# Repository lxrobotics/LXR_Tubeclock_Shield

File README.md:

LXRobotics P4 TubeClockShield
==============

# Image

# Description

A Tube Clock is defined as a clock showing the time on a so-called Vacuum Fluorescent Display (VFD). The exact operation of VFDs is described on Wikipedia vividly. The VFDs were developed in the 1960s in Japan and replaced the Nixie tubes which were functioning based on glow lamps principle. Today VFDs, because of their retro looks, are primarily used by hobbyists for clocks construction and other electronic projects. The LXRobotics Tubeclock Shield allows, in combination with an Arduino Uno Board, the construction of such tube clock. For the quick start, Arduino libraries are available with sample programs.

**Features**

* Tube voltage adjustable from 30 to 70 V
* I2C-Real Time Clock  (RTC) for clock functionality
* Brightness sensor (LDR =Light Dependent Resistor)
* Temperature sensor (NTC-Thermistor)
* Connections for 2 button/switch
* Connection for external backup baterry for keeping the current time also at power failure (external backup battery is not included in the delivery)
* Exclusively screw terminals for simple yet stable connection of cables to the board available
* Arduino Library available for control of Tubeclock Shield with example programms
* Arduino Library available for the usage of Tubeclock Shield with a IV-18 Tube
* Arduino Library for conversion of the temperature sensor - tube data in °C

# Videos

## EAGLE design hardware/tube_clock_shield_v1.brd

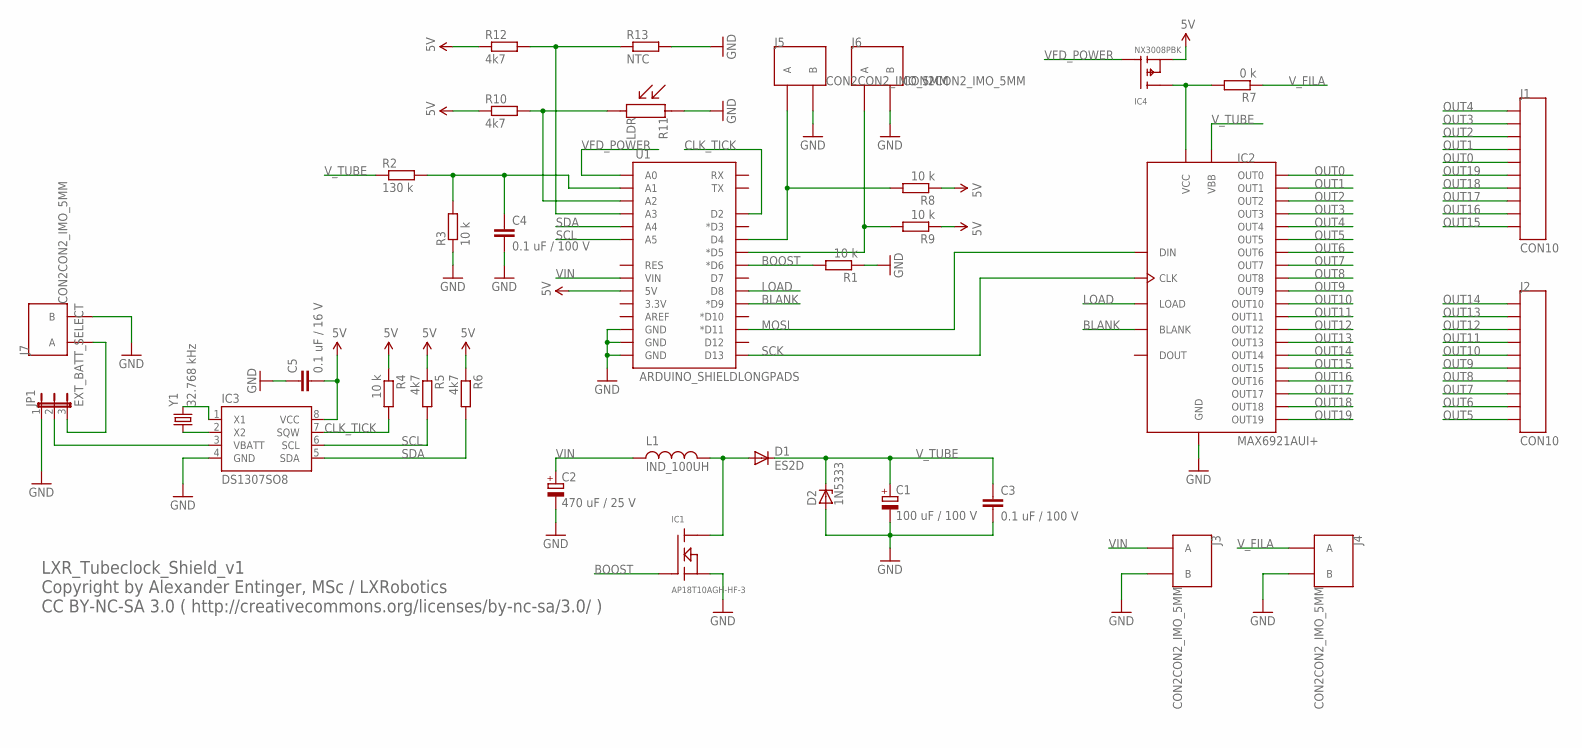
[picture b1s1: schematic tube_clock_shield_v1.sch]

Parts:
C1: 100 uF / 100 V; E5-10,5
C2: 470 uF / 25 V; E5-10,5
C3, C4: 0.1 uF / 100 V; C0805
C5: 0.1 uF / 16 V; C0805
D1: ES2D; SMB
D2: 1N5333; C1702-15
IC1: AP18T10AGH-HF-3; TO252
IC2: MAX6921AUI+; TSSOP28
IC3: DS1307SO8; SO08
IC4: NX3008PBK; SOT23
J1, J2: CON10
J3, J4, J5, J6, J7: CON2CON2_IMO_5MM; CON2_IMO
JP1: EXT_BATT_SELECT; JP2
L1: IND_100UH; LEISTUNGS_INDUKTIVITAET_PACKAGE
R1, R3, R4, R8, R9: 10 k; R0805
R2: 130 k; R0805
R5, R6, R10, R12: 4k7; R0805
R7: 0 k; R0805
R11: LDR
R13: NTC; R0805
U1: ARDUINO_SHIELDLONGPADS; DUEMILANOVE_SHIELD_LONGPADS
Y1: 32.768 kHz; TC26HEZ

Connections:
5V: C5.2, IC3.8 (VCC), IC4.2 (S), R4.1, R5.1, R6.1, R8.1, R9.1, R10.1, R12.1, U1.5V
BLANK: IC2.20 (BLANK), U1.D9 (*D9)
BOOST: IC1.G, R1.2, U1.D6 (*D6)
CLK_TICK: IC3.7 (SQW), R4.2, U1.D2
EXT_BATT: J7.P$1 (A), JP1.3
GND: C1.-, C2.-, C3.2, C4.2, C5.1, D2.A, IC1.S, IC2.21 (GND), IC3.4 (GND), J3.P$2 (B), J4.P$2 (B), J5.P$2 (B), J6.P$2 (B), J7.P$2 (B), JP1.1, R1.1, R3.1, R11.P$1, R13.2, U1.GND@0 (GND), U1.GND@1 (GND), U1.GND@2 (GND)
LOAD: IC2.23 (LOAD), U1.D8
MOSI: IC2.6 (DIN), U1.D11 (*D11)
unnamed: D1.A, IC1.D, L1.P$2
unnamed: C4.1, R2.2, R3.2, U1.A1
unnamed: IC3.2 (X2), Y1.1
unnamed: IC3.1 (X1), Y1.2
unnamed: IC2.7 (VCC), IC4.3 (D), R7.2
unnamed: J6.P$1 (A), R9.2, U1.D5 (*D5)
unnamed: IC3.3 (VBATT), JP1.2
unnamed: J5.P$1 (A), R8.2, U1.D4
unnamed: R10.2, R11.P$2, U1.A2
unnamed: R12.2, R13.1, U1.A3
OUT0: IC2.5 (OUT0), J1.P$5
OUT1: IC2.4 (OUT1), J1.P$4
OUT2: IC2.3 (OUT2), J1.P$3
OUT3: IC2.2 (OUT3), J1.P$2
OUT4: IC2.1 (OUT4), J1.P$1
OUT5: IC2.28 (OUT5), J2.P$10
OUT6: IC2.27 (OUT6), J2.P$9
OUT7: IC2.26 (OUT7), J2.P$8
OUT8: IC2.25 (OUT8), J2.P$7
OUT9: IC2.24 (OUT9), J2.P$6
OUT10: IC2.19 (OUT10), J2.P$5
OUT11: IC2.18 (OUT11), J2.P$4
OUT12: IC2.17 (OUT12), J2.P$3
OUT13: IC2.16 (OUT13), J2.P$2
OUT14: IC2.15 (OUT14), J2.P$1
OUT15: IC2.14 (OUT15), J1.P$10
OUT16: IC2.13 (OUT16), J1.P$9
OUT17: IC2.12 (OUT17), J1.P$8
OUT18: IC2.11 (OUT18), J1.P$7
OUT19: IC2.10 (OUT19), J1.P$6
SCK: IC2.22 (CLK), U1.D13
SCL: IC3.6 (SCL), R5.2, U1.A5
SDA: IC3.5 (SDA), R6.2, U1.A4
VFD_POWER: IC4.1 (G), U1.A0
VIN: C2.+, J3.P$1 (A), L1.P$1, U1.VIN
V_FILA: J4.P$1 (A), R7.1
V_TUBE: C1.+, C3.1, D1.C, D2.C, IC2.8 (VBB), R2.1

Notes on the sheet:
LXR_Tubeclock_Shield_v1 Copyright by Alexander Entinger, MSc / LXRobotics CC BY-NC-SA 3.0 ( http://creativecommons.org/licenses/by-nc-sa/3.0/ )

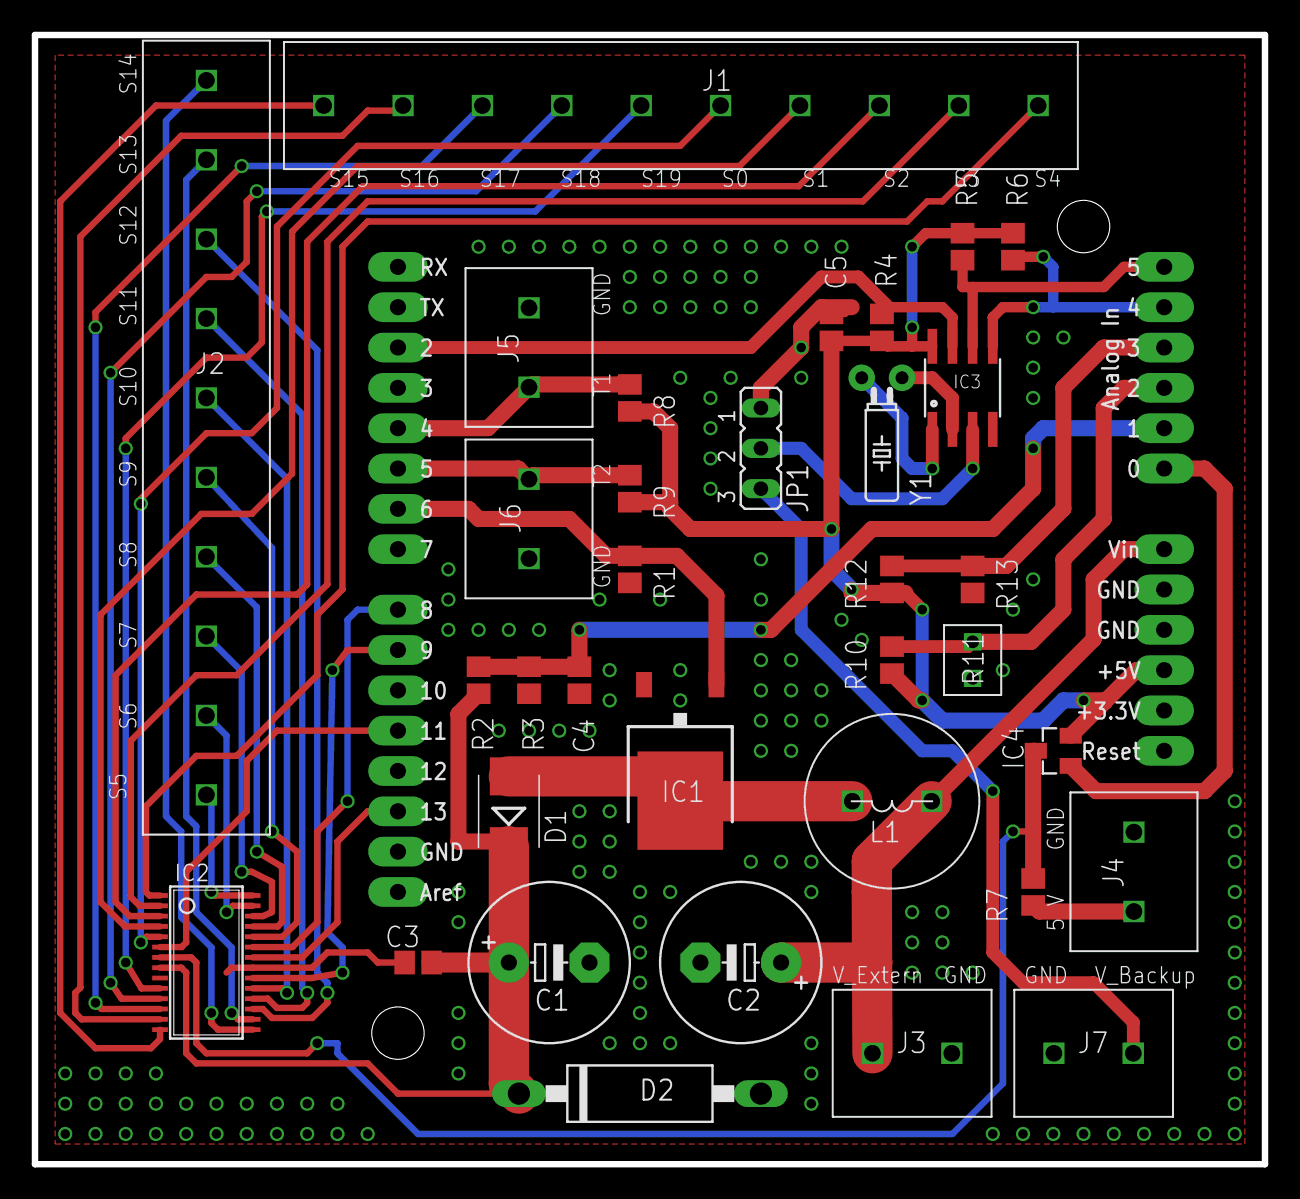
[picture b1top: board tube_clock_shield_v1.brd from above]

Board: 2 copper layers, 77.5 x 71.1 mm, 35 parts (0 on the bottom side), 45 nets.

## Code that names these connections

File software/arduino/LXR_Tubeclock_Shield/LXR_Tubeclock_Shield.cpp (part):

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
/* DEFINES */

// BOOST = D6 = PD6 = OC0A
#define BOOST_DDR	        (DDRD)
#define BOOST_PORT	        (PORTD)
#define BOOST		        (1<<6)
// VFD_POWER = A0 = ADC0 = PC0
#define VFD_POWER_DDR	        (DDRC)
#define VFD_POWER_PORT	        (PORTC)
#define VFD_POWER		(1<<0)
// BLANK = D9 = PB1
#define BLANK_DDR		(DDRB)
#define BLANK_PORT		(PORTB)
#define BLANK			(1<<1)
// LOAD = D8 = PB0
#define LOAD_DDR		(DDRB)
#define LOAD_PORT		(PORTB)
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
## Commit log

2014-01-15 initial checkin of brushless motorshield
2017-06-27 Adding hardware and images

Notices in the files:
software/arduino/LXR_Tubeclock_Shield/LXR_Tubeclock_Shield.cpp:
@license Attribution-NonCommercial-ShareAlike 3.0 Unported (CC BY-NC-SA 3.0) ( http://creativecommons.org/licenses/by-nc-sa/3.0/ )
README.md:
License: CC BY-NC-SA 4.0
parts and their libraries:
SparkFun-Boards: Licensing: CC v3.0 Share-Alike You are welcome to use this library for commercial purposes.
